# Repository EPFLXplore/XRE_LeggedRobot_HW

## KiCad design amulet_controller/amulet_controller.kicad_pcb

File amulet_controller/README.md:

<p align="center" width="100%">
  <source media="(prefers-color-scheme: dark)" width="33%" srcset="./Logos/amulet_logo_light.svg">
  <source media="(prefers-color-scheme: light)" width="33%" srcset="./Logos/amulet_logo.svg">
  
</p>

<h1 align="center">Λ M U L E T</h1>

ΛMULET is a high-power brushless motor controller, compatible with the [moteus firmware](https://github.com/mjbots/moteus). It was specifically designed to be integrated in [EPFL Xplore](https://github.com/EPFLXplore)'s Legged Robot actuators.

***

## SPECIFICATIONS

| Parameter | ΛMULET V1.0 | 
| --- | --- |
| Voltage Input | 12-44V |
| Peak Electrical Power | TBD |
| Mass | TBD |
| Peak Phase Current | 100A |
| Communication | 5Mbps CAN-FD |
| Cooling | 12V Fan |
| Positioning | 2x Onboard 14-bit Encoders |
| Control rate | 15-30kHz |
| PWM Switching Rate | 15-60kHz |
| MCU | STM32G474 |
| Dimensions | 69.7 x 76.7mm |

***

## DIRECTORY STRUCTURE

```
amulet_controller
├── Computations     # Misc calculations
├── DXF_SVG          # Vector graphics
├── Images           # Pictures and screenshots
├── Logos            # Xplore and Amulet logos
├── Manufacturing
│   |── Assembly     # Position files, BOM, assembly document
|   |   └── ibom     # HTML BOM
|   └── Fabrication  # Fabrication document and testpoints positions
|       └── Gerbers  # Gerbers
├── STEP_Blender     # 3D STEP and pcb2blender file
├── Schematic        # PDF of schematic
├── Templates        # Title block templates
└── lib
    |── 3d_models    # Component 3D models
    |── lib_fp       # Footprint libraries
    └── lib_sym      # Symbol libraries
```

***

## FIRMWARE

[Associated firmware](https://github.com/EPFLXplore/XRE_moteus/tree/amulet) is forked from the [moteus](https://github.com/mjbots/moteus) repository.

***

## CREDITS

Schematic is hugely inspired by the moteus controllers designed by Josh Pieper. They were modified to meet our own specifications, and to follow what I personally consider good layout practices.

***

## PHOTOS

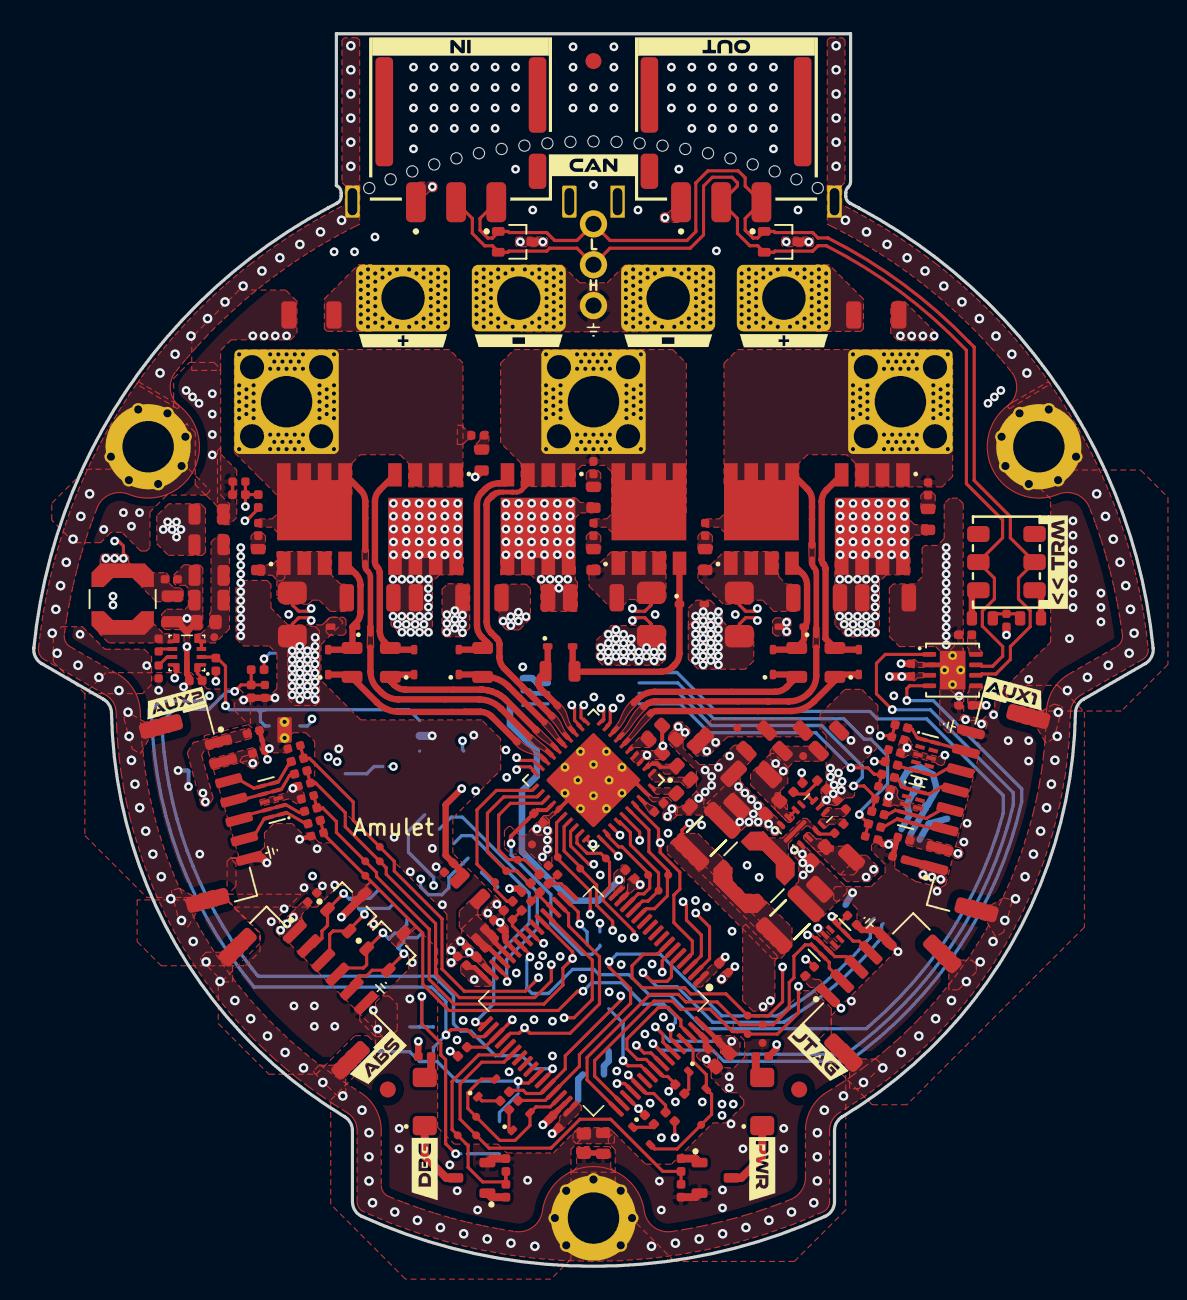
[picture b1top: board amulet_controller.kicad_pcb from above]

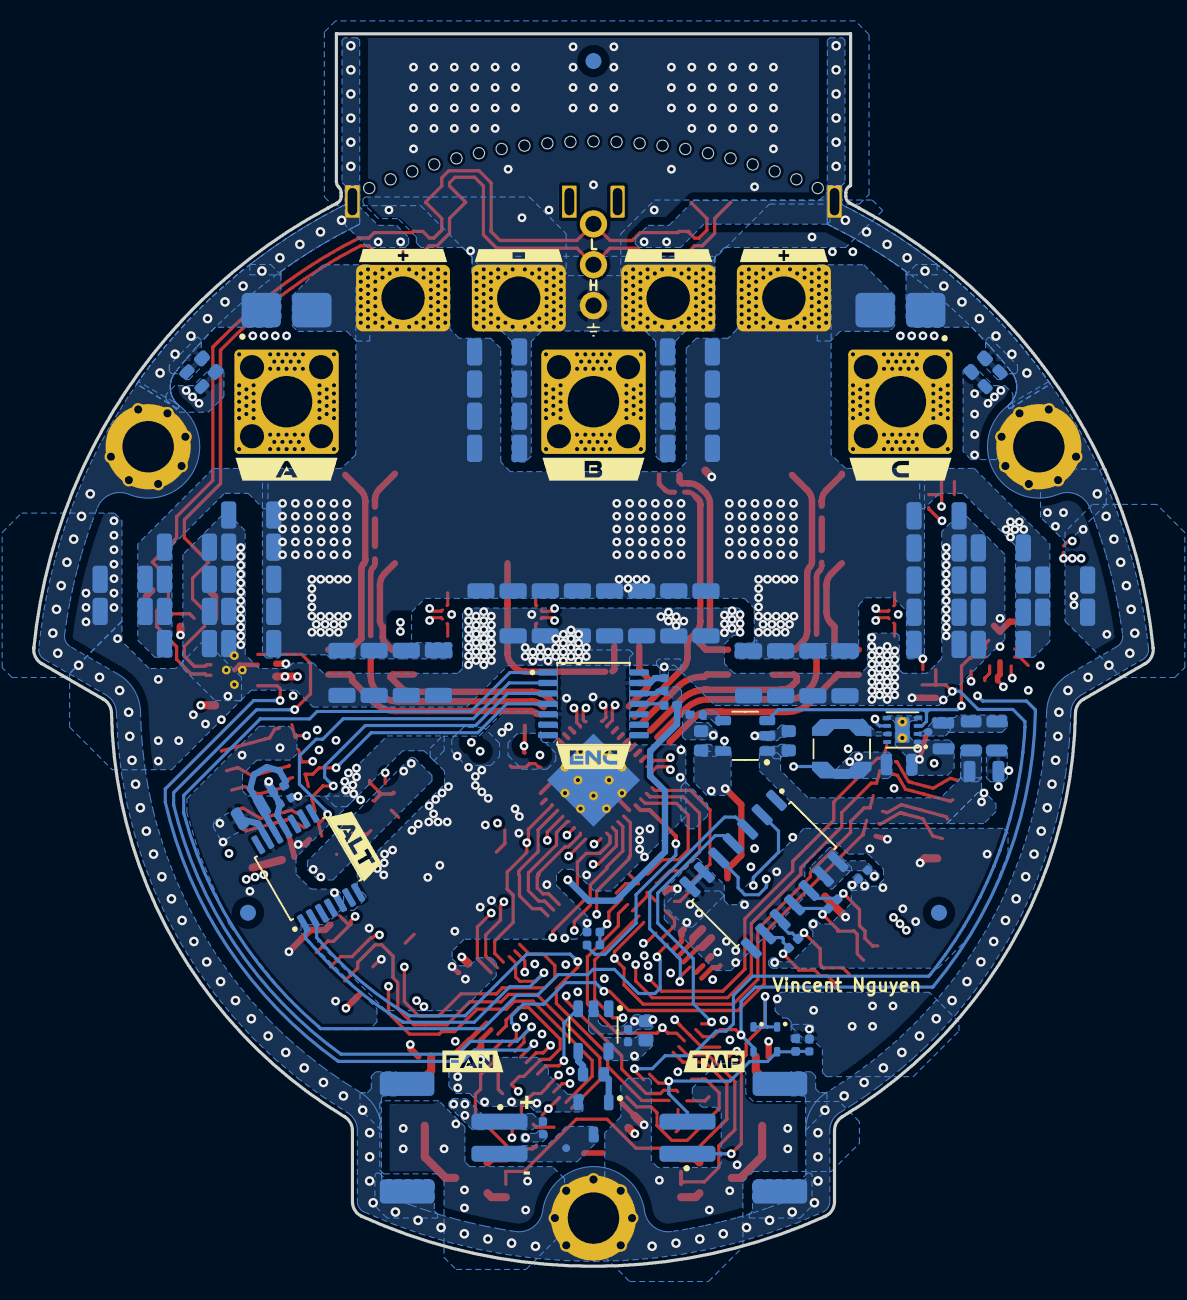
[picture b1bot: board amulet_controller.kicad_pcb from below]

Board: 6 copper layers, 69.7 x 76.7 mm, 413 parts (120 on the bottom side), 141 nets.

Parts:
C1, C84, C110: 4u7 X7R 16V; C_0603_1608_DensityHigh
C2, C6, C9, C24, C26: 1u X7R 10V; C_0402_1005_DensityHigh
C3, C4, C5, C8, C10, C11, C27, C28, C29, C101, C102, C103, C104, C105, C107, C108, C109, C111, C112, C113, C114, C115, C125, C126, C127, C128: 100n X7R 50V; C_0402_1005_DensityHigh
C7: 4u7 X5R 25V; C_0402_1005_DensityHigh
C12, C13, C14: 1n X7R 25V; C_0402_1005_DensityHigh
C15, C16, C17, C18, C20, C45, C52: 2u2 X7R 100V; R_0805_2012_DensityHigh
C19, C21, C31, C32, C33, C34, C35, C36, C39, C40, C41, C42, C43, C44, C46, C47, C48, C49, C50, C51, C53, C54, C55, C57, C58, C59, C61, C62, C63, C64, C65, C66, C67, C68, C69, C70, C71, C72, C73, C74, C75, C77, C78, C79, C80, C81, C82, C85, C86, C87: 4u7 X7R 100V; C_1206_3216_DensityHigh
C22, C92: 100n X7R 100V; C_0603_1608_DensityHigh
C23, C25: 220n X7S 100V; C_0603_1608_DensityHigh
C30, C38: 15u X7R 25V; C_1210_3225_DensityHigh
C37, C83: 22u X7R 10V; C_0805_2012_DensityHighest
C56, C106: 10u X7R 25V; C_0805_2012_DensityHighest
C60, C88, C93: 1u X7R 25V; C_0603_1608_DensityHigh
C76: 10n X7R 100V; C_0402_1005_DensityHigh
C89, C96, C98, C100: 4u7 X7R 100V; C_1206_3216_DensityHighest
C90: 100n X7R 16V; C_0402_1005_DensityHigh
C91: 47n X7R 100V; C_0603_1608_DensityHigh
C94: 1u X7R 6.3V; C_0402_1005_DensityHigh
C95, C97, C99: 100n X7R 100V; C_1206_3216_DensityHighest
C116, C117, C118, C119, C120, C121, C122, C123, C124, C133, C134, C135, C136, C137, C138: 3n3 X7R 100V; C_0402_1005_DensityHigh
C129: 4n7 X7R 100V; C_0402_1005_DensityHigh
C130, C131, C132: 1n X7R 1kV; C_0603_1608_DensityHigh
D1, D2: SMBJ51CD-M3/H; DIOM4336X24N
D3, D4, D5, D6, D7, D8, D9, D10, D11, D14, D15, D19, D20, D21, D22: BAT41KFILM; D_SOD-523
D12: YELLOW; LED_SM1206
D13: GREEN; LED_SM1206
D16, D17: PESD4USB5B-TBSX; SOT1176D
D18, D26: PESD4USB3U-TBSX; SOT1176D
D23, D27: CDSOT23-SM712; SOT95P230X110-3N
D24, D25: PESD2CANFD24V-UX; SOT95P230X117-3N
FB1, FB2, FB3, FB4: 1k @ 100MHz; R_0805_2012_DensityHigh
FM1, FM2, FM3, FM4, FM5, FM6: Fiducial; Fiducial_1mm_Mask2mm
H1, H2, H3: M3; MountingHole_3.2mm_M3_Pad_Via
J1: XT60PW-F; AMASS_XT60PW-F_1x02_P7.20mm_Horizontal
J2: XT60PW-M; AMASS_XT60PW-M_1x02_P7.20mm_Horizontal
J3: Phase A; Pad_Square_Vias_6.5x6.5mm
J4: Phase B; Pad_Square_Vias_6.5x6.5mm
J5: Phase C; Pad_Square_Vias_6.5x6.5mm
J6: SM08B-GHS-TB; JST_GH_SM08B-GHS-TB_1x08-1MP_P1.25mm_Horizontal
J7: SM07B-GHS-TB; JST_GH_SM07B-GHS-TB_1x07-1MP_P1.25mm_Horizontal
J8, J9: S2B-PH-SM4-TB; JST_PH_S2B-PH-SM4-TB_1x02-1MP_P2.00mm_Horizontal
J10: SM06B-GHS-TB; JST_GH_SM06B-GHS-TB_1x06-1MP_P1.25mm_Horizontal
J11: PTH 01x03 2.54mm; PTH_1x03_P2.54mm
J12, J13: Nano-Fit 1x03; 1054301203
J14: SM05B-GHS-TB; JST_GH_SM05B-GHS-TB_1x05-1MP_P1.25mm_Horizontal
L1, L2: 22u; L_Coilcraft_LPS4018
L3: 2u2; L_Coilcraft_LPS3314
MB1, MB2, MB3, MB4, MB5, MB6, MB7, MB8, MB9, MB10, MB11, MB12, MB13, MB14, MB15, MB16, MB17, MB18, MB19, MB20, MB21: mousebites_single_0.7mm
NT1: FB_5V; NetTie-2_SMD_Pad0.2mm
NT2: FB_12V; NetTie-2_SMD_Pad0.2mm
NT3: VOS_3V3; NetTie-2_SMD_Pad0.2mm
NT4: SRC_HS_A; NetTie-2_SMD_Pad0.4mm
NT5: SHNTA_P; NetTie-2_SMD_Pad0.2mm
NT6: SHNTA_N; NetTie-2_SMD_Pad0.2mm
NT7: SRC_HS_B; NetTie-2_SMD_Pad0.3mm
NT8: SHNTB_P; NetTie-2_SMD_Pad0.2mm
NT9: SHNTB_N; NetTie-2_SMD_Pad0.2mm
NT10: SRC_HS_C; NetTie-2_SMD_Pad0.4mm
NT11: SHNTC_P; NetTie-2_SMD_Pad0.2mm
NT12: SHNTC_N; NetTie-2_SMD_Pad0.2mm
NT13: NTC_MOT_H; NetTie-2_SMD_Pad0.2mm
NT14: NTC_MOT_L; NetTie-2_SMD_Pad0.2mm
Q1, Q2, Q3, Q4, Q5, Q6: TPW1R306PL,L1Q; 2-5S1A
Q7, Q8, Q9: PMV90ENER; SOT-23-3
R1, R2, R3: 22R 1%; R_0402_1005_DensityHigh
R4, R31, R32: 0R; R_0402_1005_DensityHigh
R5, R19, R20, R21, R24, R29: 100k 1%; R_0402_1005_DensityHigh
R6: 9k09 1%; R_0402_1005_DensityHigh
R7, R27, R33: 10k 1%; R_0402_1005_DensityHigh
R8, R9, R28, R44, R45, R46, R47: 2k 1%; R_0402_1005_DensityHigh
R10, R11, R13, R14, R16, R17: 7R5 1% 1/2W; R_0805_2012_DensityHigh
R12, R15, R18: 0m5 1% 2W; HCS1206FTL500
R22, R23, R25, R35, R36, R37, R38, R39, R40, R41, R42, R43, R48, R49: 100R 1% 1/5W; R_0402_1005_DensityHigh
R26: 150R 1% 1/5W; R_0402_1005_DensityHigh
R30: 4k7 1%; R_0402_1005_DensityHigh
R34: 10R 1%; R_0603_1608_DensityHigh
R50, R51: 60R4 1% 1/4W; R_0603_1608_DensityHigh
R52, R53, R54: 0R; R_0603_1608_DensityHigh
R55, R56, R57, R58, R59, R60: 5R 1% 0.4W; R_0603_1608_DensityHigh
SW1: CAS-220TA; CAS-220A_NDC-L
TH1: 47k 1% NTC; R_0402_1005_DensityHigh
TP1: MOTOR_ENABLE; TestPoint_Pad_D0.5mm
TP2: MOTOR_HIZ; TestPoint_Pad_D0.5mm
TP3: MOTOR_FAULT; TestPoint_Pad_D0.5mm
TP4: DRV_SCLK; TestPoint_Pad_D0.5mm
TP5: DRV_MISO; TestPoint_Pad_D0.5mm
TP6: DRV_MOSI; TestPoint_Pad_D0.5mm
TP7: DRV_CS; TestPoint_Pad_D0.5mm
TP8: PWM_PHASEA; TestPoint_Pad_D0.5mm
TP9: PWM_PHASEB; TestPoint_Pad_D0.5mm
TP10: PWM_PHASEC; TestPoint_Pad_D0.5mm
TP11: SOA; TestPoint_Pad_D0.5mm
TP12: SOB; TestPoint_Pad_D0.5mm
TP13: SOC; TestPoint_Pad_D0.5mm
TP14: SWDIO; TestPoint_Pad_D0.5mm
TP15: SWCLK; TestPoint_Pad_D0.5mm
TP16: NRST; TestPoint_Pad_D0.5mm
TP17: AUX1_A; TestPoint_Pad_D0.5mm
TP18: AUX1_B; TestPoint_Pad_D0.5mm
TP19: AUX1_C; TestPoint_Pad_D0.5mm
TP20: AUX1_D; TestPoint_Pad_D0.5mm
TP21: AUX1_E; TestPoint_Pad_D0.5mm
TP22: AUX1_I2C_PULLUP; TestPoint_Pad_D0.5mm
TP23: POS_SENSOR_CS; TestPoint_Pad_D0.5mm
TP24: AUX2_A; TestPoint_Pad_D0.5mm
TP25: AUX2_B; TestPoint_Pad_D0.5mm
TP26: AUX2_C; TestPoint_Pad_D0.5mm
TP27: AUX2_D; TestPoint_Pad_D0.5mm
TP28: AUX2_I2C_PULLUP; TestPoint_Pad_D0.5mm
TP29: RS422_RE; TestPoint_Pad_D0.5mm
TP30: RS422_DE; TestPoint_Pad_D0.5mm
TP31: LED_DBG; TestPoint_Pad_D0.5mm
TP32: LED_PWR; TestPoint_Pad_D0.5mm
TP33: FD_CAN_RX; TestPoint_Pad_D0.5mm
TP34: FDCAN_TX; TestPoint_Pad_D0.5mm
TP35: FAN_CTRL; TestPoint_Pad_D0.5mm
TP36: SENSE_TEMP_MOT; TestPoint_Pad_D0.5mm
TP37: SENSE_TEMP_FET; TestPoint_Pad_D0.5mm
TP38: SENSE_VBAT; TestPoint_Pad_D0.5mm
TP39, TP40, TP41: +VBAT; TestPoint_Pad_D0.5mm
TP42: F_VIN_12V; TestPoint_Pad_D0.5mm
TP43: F_VIN_5V; TestPoint_Pad_D0.5mm
TP44: F_VIN_3V3; TestPoint_Pad_D0.5mm
TP45: +12V; TestPoint_Pad_D0.5mm
TP46, TP47: +5V; TestPoint_Pad_D0.5mm
TP48, TP49, TP50: +3V3; TestPoint_Pad_D0.5mm
TP51: +A3V3; TestPoint_Pad_D0.5mm
TP52, TP53, TP54, TP55, TP56, TP57, TP58: GND; TestPoint_Pad_D0.5mm
TP59: GHA; TestPoint_Pad_D0.4mm
TP60: GLA; TestPoint_Pad_D0.4mm
TP61: SHA; TestPoint_Pad_D0.4mm
TP62: GHB; TestPoint_Pad_D0.4mm
TP63: GLB; TestPoint_Pad_D0.4mm
TP64: SHB; TestPoint_Pad_D0.4mm
TP65: GHC; TestPoint_Pad_D0.4mm
TP66: GLC; TestPoint_Pad_D0.4mm
TP67: SHC; TestPoint_Pad_D0.4mm
TP68: SA_P; TestPoint_Pad_D0.5mm
TP69: SA_N; TestPoint_Pad_D0.5mm
TP70: SB_P; TestPoint_Pad_D0.5mm
TP71: SB_N; TestPoint_Pad_D0.5mm
TP72: SC_P; TestPoint_Pad_D0.5mm
TP73: SC_N; TestPoint_Pad_D0.5mm
TP74: FAN_SW; TestPoint_Pad_D0.5mm
U1: STM32G474RET3; LQFP-64_10x10mm_P0.5mm
U2: LMR36506MSC5RPERQ1; LMR36503
U3: LMR36006FSCQ; LMR36006
U4: TPS62172DSG; WSON-8-1EP_2x2mm_P0.5mm_EP0.9x1.6mm_ThermalVias
U5: LP2992IM5-3.3/NOPB; SOT95P280X145-5N
U6: DRV8353FS; WQFN-40-1EP_6x6mm_P0.5mm_EP4.15x4.15mm_ThermalVias
U7: AS5047P; SOP-14_4.4x5mm_P0.65mm_H1.2mm
U8: AS5048B; SOP-14_4.4x5mm_P0.65mm_H1.2mm
U9: SN65HVD35DR; SOIC-14 5.4mm
U10: TCAN1051HGVDRBRQ1; HVSON-8-1EP_3x3mm_P0.65mm_EP1.6x2.4mm_ThermalVias
U11: DGD0216WT-7; SOT-23-5
kibuzzard-657CE6B7: G***; kibuzzard-657CE6B7
kibuzzard-657CE6F4: G***; kibuzzard-657CE6F4
kibuzzard-657CE8E9: G***; kibuzzard-657CE8E9
kibuzzard-657CE8F0: G***; kibuzzard-657CE8F0
kibuzzard-657CE701: G***; kibuzzard-657CE701
kibuzzard-657CE738: G***; kibuzzard-657CE738
kibuzzard-657DB620: G***; kibuzzard-657DB620
kibuzzard-657EBC7A: G***; kibuzzard-657EBC7A
kibuzzard-657EBC30: G***; kibuzzard-657EBC30
kibuzzard-657EBCD6: G***; kibuzzard-657EBCD6
kibuzzard-657EBD3F: G***; kibuzzard-657EBD3F
kibuzzard-657EBDD6: G***; kibuzzard-657EBDD6
kibuzzard-657EBE81: G***; kibuzzard-657EBE81
kibuzzard-657EBEA6: G***; kibuzzard-657EBEA6
kibuzzard-657F78ED, kibuzzard-657F78ED#2, kibuzzard-657F78ED#3, kibuzzard-657F78ED#4: G***; kibuzzard-657F78ED
kibuzzard-657F7953, kibuzzard-657F7953#2, kibuzzard-657F7953#3, kibuzzard-657F7953#4: G***; kibuzzard-657F7953
kibuzzard-65803F12: G***; kibuzzard-65803F12
kibuzzard-658032A4: G***; kibuzzard-658032A4
kibuzzard-6580330B: G***; kibuzzard-6580330B
kibuzzard-65807142: G***; kibuzzard-65807142
kibuzzard-65807156: G***; kibuzzard-65807156

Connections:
+3V3: C1.1, C3.1, C4.1, C5.1, C8.1, C9.1, C83.1, C104.1, C105.1, C107.1, C108.1, C114.1, C115.1, C127.1, J6.2, J7.2, J14.1, L3.2, NT3.2, R8.1, R9.1, R31.1, R32.1, TP48.1, TP49.1, TP50.1, U1.1 (VBAT), U1.16 (VDD), U1.32 (VDD), U1.48 (VDD), U1.64 (VDD), U7.12 (VDD3V3), U8.11 (VDD5V), U9.13 (VCC), U9.14 (VCC), U10.5 (VIO)
+5V: C29.1, C37.1, C45.1, C60.1, C109.1, C110.1, C111.1, C112.1, C113.1, C126.1, FB4.1, J6.1, J7.1, J10.1, L1.2, NT1.1, R7.2, R23.2, R26.1, TP46.1, TP47.1, U5.1 (VIN), U10.3 (VCC), U11.5 (VCC)
+12V: C30.1, C38.1, C125.1, J9.1, L2.2, NT2.2, TP45.1
+A3V3: C2.1, C84.1, C90.1, D14.1 (K), D15.1 (K), FB1.1, NT13.1, R19.1, TH1.1, TP51.1, U5.5 (VOUT), U6.24 (VREF)
+VBAT: C15.1, C16.1, C31.1, C32.1, C33.1, C34.1, C35.1, C36.1, C39.1, C40.1, C41.1, C42.1, C43.1, C44.1, C46.1, C47.1, C48.1, C49.1, C50.1, C51.1, C53.1, C54.1, C55.1, C57.1, C58.1, C59.1, C61.1, C62.1, C63.1, C64.1, C65.1, C66.1, C67.1, C68.1, C69.1, C70.1, C71.1, C72.1, C73.1, C74.1, C75.1, C77.1, C78.1, C79.1, C80.1, C81.1, C82.1, C85.1, C86.1, C87.1, C88.1, C89.1, C92.1, C95.1, C96.1, C97.1, C98.1, C99.1, C100.1, D1.2 (A2), D2.2 (A2), FB2.1, FB3.1, J1.2, J2.2, Q1.5 (D), Q1.6 (D), Q1.7 (D), Q1.8 (D), Q3.5 (D), Q3.6 (D), Q3.7 (D), Q3.8 (D), Q5.5 (D), Q5.6 (D), Q5.7 (D), Q5.8 (D), R29.1, R58.2, R59.2, R60.2, TP39.1, TP40.1, TP41.1, U6.3 (VM), U6.4 (VDRAIN)
/Project Architecture/Interface - FD-CAN/FDCAN_N: D24.1 (K1), D25.1 (K1), J11.3, J12.3, J13.3, SW1.2 (B), U10.6 (CANL)
/Project Architecture/Interface - FD-CAN/FDCAN_P: D24.2 (K2), D25.2 (K2), J11.2, J12.2, J13.2, SW1.5 (B), U10.7 (CANH)
/Project Architecture/Interface - FD-CAN/FDCAN_RX: TP33.1, U1.58 (PB5), U10.4 (RXD)
/Project Architecture/Interface - FD-CAN/FDCAN_S: R33.1, U10.8 (S)
/Project Architecture/Interface - FD-CAN/FDCAN_TX: TP34.1, U1.59 (PB6), U10.1 (TXD)
/Project Architecture/Interface - Fan Control/FAN_GATE: Q9.1 (G), R34.2
/Project Architecture/Interface - Fan Control/FAN_OUT: R34.1, U11.4 (OUT)
/Project Architecture/Interface - Fan Control/FAN_SW: J9.2, Q9.3 (D), TP74.1
/Project Architecture/Interface - Interconnects/AUX1P_A: D18.5 (K), D18.6 (K), J6.3, R35.1
/Project Architecture/Interface - Interconnects/AUX1P_B: D18.4 (K), D18.7 (K), J6.4, R36.1
/Project Architecture/Interface - Interconnects/AUX1P_C: D18.1 (K), D18.10 (K), J6.5, R37.1
/Project Architecture/Interface - Interconnects/AUX1P_D: D16.5 (K), D16.6 (K), J6.6, R38.1
/Project Architecture/Interface - Interconnects/AUX1P_E: D16.1 (K), D16.10 (K), J6.7, R39.1
/Project Architecture/Interface - Interconnects/AUX1_A: C124.1, R35.2, TP17.1, U1.19 (PA5), U1.36 (PB14), U7.2 (CLK)
/Project Architecture/Interface - Interconnects/AUX1_B: C122.1, R36.2, TP18.1, U1.57 (PB4), U7.3 (MISO)
/Project Architecture/Interface - Interconnects/AUX1_C: C120.1, R37.2, TP19.1, U1.21 (PA7), U7.4 (MOSI)
/Project Architecture/Interface - Interconnects/AUX1_D: C118.1, R38.2, R44.2, TP20.1, U1.51 (PA15), U9.2 (R)
/Project Architecture/Interface - Interconnects/AUX1_D_K: D19.1 (K), R44.1
/Project Architecture/Interface - Interconnects/AUX1_E: C116.1, R39.2, R46.2, TP21.1, U1.56 (PB3), U1.62 (PB9), U9.5 (D)
/Project Architecture/Interface - Interconnects/AUX1_E_K: D21.1 (K), R46.1
/Project Architecture/Interface - Interconnects/AUX1_I2C_PULLUP: D19.2 (A), D21.2 (A), TP22.1, U1.61 (PB8)
/Project Architecture/Interface - Interconnects/AUX2P_A: D17.5 (K), D17.6 (K), J7.3, R40.1
/Project Architecture/Interface - Interconnects/AUX2P_B: D17.4 (K), D17.7 (K), J7.4, R41.1
/Project Architecture/Interface - Interconnects/AUX2P_C: D17.2 (K), D17.9 (K), J7.5, R42.1
/Project Architecture/Interface - Interconnects/AUX2P_D: D17.1 (K), D17.10 (K), J7.6, R43.1
/Project Architecture/Interface - Interconnects/AUX2_A: C123.1, R40.2, TP24.1, U1.6 (PF1)
/Project Architecture/Interface - Interconnects/AUX2_B: C121.1, R41.2, R45.2, TP25.1, U1.5 (PF0), U1.44 (PA10), U8.1 (SDA)
/Project Architecture/Interface - Interconnects/AUX2_B_K: D20.1 (K), R45.1
/Project Architecture/Interface - Interconnects/AUX2_C: C119.1, R42.2, R47.2, TP26.1, U1.22 (PC4), U1.45 (PA11), U8.2 (SCL)
/Project Architecture/Interface - Interconnects/AUX2_C_K: D22.1 (K), R47.1
/Project Architecture/Interface - Interconnects/AUX2_D: C117.1, R43.2, TP27.1, U1.60 (PB7)
/Project Architecture/Interface - Interconnects/AUX2_I2C_PULLUP: D20.2 (A), D22.2 (A), TP28.1, U1.46 (PA12)
/Project Architecture/Interface - Interconnects/CAN_TERM_B: R51.2, SW1.4 (A)
/Project Architecture/Interface - Interconnects/CAN_TERM_MID: C129.1, R50.2, R51.1
/Project Architecture/Interface - Interconnects/CAN_TERM_T: R50.1, SW1.1 (A)
/Project Architecture/Interface - Interconnects/NRST: C128.1, D26.1 (K), D26.10 (K), J14.4, TP16.1, U1.7 (PG10)
/Project Architecture/Interface - Interconnects/NTC_MOT_H: J8.1, NT13.2
/Project Architecture/Interface - Interconnects/NTC_MOT_L: J8.2, NT14.2
/Project Architecture/Interface - Interconnects/POS_SENSOR_CS: TP23.1, U1.26 (PB2), U7.1 (~CS)
/Project Architecture/Interface - Interconnects/RS422_D+: D23.2 (A2), J10.5, R49.2, U9.9 (Y)
/Project Architecture/Interface - Interconnects/RS422_D-: D23.1 (A1), J10.4, R49.1, U9.10 (Z)
/Project Architecture/Interface - Interconnects/RS422_R+: D27.1 (A1), J10.2, R48.1, U9.12 (A)
/Project Architecture/Interface - Interconnects/RS422_R-: D27.2 (A2), J10.3, R48.2, U9.11 (B)
/Project Architecture/Interface - Interconnects/SWCLK: D26.4 (K), D26.7 (K), J14.3, TP15.1, U1.50 (PA14)
/Project Architecture/Interface - Interconnects/SWDIO: D26.5 (K), D26.6 (K), J14.2, TP14.1, U1.49 (PA13)
/Project Architecture/Interface - RS-422/RS422_DE: TP30.1, U1.33 (PB11), U9.4 (DE)
/Project Architecture/Interface - RS-422/RS422_~RE: TP29.1, U1.30 (PB10), U9.3 (~RE)
/Project Architecture/MCU - IOs/BOARD_VERSION: R19.2, R20.1, U1.18 (PA4)
/Project Architecture/MCU - IOs/DRV_CS: TP7.1, U1.24 (PB0), U6.30 (nSCS)
/Project Architecture/MCU - IOs/DRV_MISO: R9.2, TP5.1, U1.53 (PC11), U6.27 (SDO)
/Project Architecture/MCU - IOs/DRV_MOSI: TP6.1, U1.2 (PC13), U6.28 (SDI)
/Project Architecture/MCU - IOs/DRV_SCLK: TP4.1, U1.52 (PC10), U6.29 (SCLK)
/Project Architecture/MCU - IOs/FAN_CTRL: TP35.1, U1.55 (PD2), U11.3 (IN)
/Project Architecture/MCU - IOs/FILTER_SOA: C12.1, R1.1, U1.17 (PA3)
/Project Architecture/MCU - IOs/FILTER_SOB: C13.1, R2.1, U1.20 (PA6)
/Project Architecture/MCU - IOs/FILTER_SOC: C14.1, R3.1, U1.25 (PB1)
/Project Architecture/MCU - IOs/LED_DBG: R21.1, R22.1, TP31.1, U1.37 (PB15)
/Project Architecture/MCU - IOs/LED_PWR: R24.1, R25.1, TP32.1, U1.38 (PC6)
/Project Architecture/MCU - IOs/MOTOR_ENABLE: TP1.1, U1.3 (PC14), U6.31 (ENABLE)
/Project Architecture/MCU - IOs/MOTOR_FAULT: R8.2, TP3.1, U1.35 (PB13), U6.26 (nFAULT)
/Project Architecture/MCU - IOs/MOTOR_HIZ: TP2.1, U1.4 (PC15), U6.33 (INLA), U6.35 (INLB), U6.37 (INLC)
/Project Architecture/MCU - IOs/PWM_PHASEA: TP8.1, U1.14 (PA2), U6.32 (INHA)
/Project Architecture/MCU - IOs/PWM_PHASEB: TP9.1, U1.13 (PA1), U6.34 (INHB)
/Project Architecture/MCU - IOs/PWM_PHASEC: TP10.1, U1.12 (PA0), U6.36 (INHC)
/Project Architecture/MCU - IOs/SENSE_TEMP_FET: C101.1, D14.2 (A), R27.1, TH1.2, TP37.1, U1.34 (PB12)
/Project Architecture/MCU - IOs/SENSE_TEMP_MOT: C102.1, D15.2 (A), NT14.1, R28.1, TP36.1, U1.42 (PA8)
/Project Architecture/MCU - IOs/SENSE_VBAT: C103.1, R29.2, R30.1, TP38.1, U1.43 (PA9)
/Project Architecture/MCU - IOs/SOA: R1.2, TP11.1, U6.23 (SOA)
/Project Architecture/MCU - IOs/SOB: R2.2, TP12.1, U6.22 (SOB)
/Project Architecture/MCU - IOs/SOC: R3.2, TP13.1, U6.21 (SOC)
/Project Architecture/MCU - Power/F_A3V3: C6.1, C7.1, C10.1, C11.1, FB1.2, U1.28 (VREF+), U1.29 (VDDA)
/Project Architecture/Motor Control - Top Level/CPH: C91.1, U6.2 (CPH)
/Project Architecture/Motor Control - Top Level/CPL: C91.2, U6.1 (CPL)
/Project Architecture/Motor Control - Top Level/DVDD: C94.1, U6.38 (DVDD)
/Project Architecture/Motor Control - Top Level/GHA: D4.1 (K), R10.2, TP59.1, U6.6 (GHA)
/Project Architecture/Motor Control - Top Level/GHB: D7.1 (K), R13.1, TP62.1, U6.15 (GHB)
/Project Architecture/Motor Control - Top Level/GHC: D10.1 (K), R16.1, TP65.1, U6.16 (GHC)
/Project Architecture/Motor Control - Top Level/GLA: D5.1 (K), R11.1, TP60.1, U6.8 (GLA)
/Project Architecture/Motor Control - Top Level/GLB: D8.1 (K), R14.1, TP63.1, U6.13 (GLB)
/Project Architecture/Motor Control - Top Level/GLC: D11.1 (K), R17.1, TP66.1, U6.18 (GLC)
/Project Architecture/Motor Control - Top Level/Motor Control - Inverter/FET_GHA: D4.2 (A), Q1.4 (G), R10.1
/Project Architecture/Motor Control - Top Level/Motor Control - Inverter/FET_GHB: D7.2 (A), Q3.4 (G), R13.2
/Project Architecture/Motor Control - Top Level/Motor Control - Inverter/FET_GHC: D10.2 (A), Q5.4 (G), R16.2
/Project Architecture/Motor Control - Top Level/Motor Control - Inverter/FET_GLA: D3.1 (K), D5.2 (A), Q2.4 (G), R11.2
/Project Architecture/Motor Control - Top Level/Motor Control - Inverter/FET_GLB: D6.1 (K), D8.2 (A), Q4.4 (G), R14.2
/Project Architecture/Motor Control - Top Level/Motor Control - Inverter/FET_GLC: D9.1 (K), D11.2 (A), Q6.4 (G), R17.2
/Project Architecture/Motor Control - Top Level/Motor Control - Inverter/PHA: C133.2, C136.1, J3.1, NT4.2, Q1.1 (S), Q1.2 (S), Q1.3 (S), Q2.5 (D), Q2.6 (D), Q2.7 (D), Q2.8 (D)
/Project Architecture/Motor Control - Top Level/Motor Control - Inverter/PHB: C134.2, C137.1, J4.1, NT7.2, Q3.1 (S), Q3.2 (S), Q3.3 (S), Q4.5 (D), Q4.6 (D), Q4.7 (D), Q4.8 (D)
/Project Architecture/Motor Control - Top Level/Motor Control - Inverter/PHC: C135.2, C138.1, J5.1, NT10.2, Q5.1 (S), Q5.2 (S), Q5.3 (S), Q6.5 (D), Q6.6 (D), Q6.7 (D), Q6.8 (D)
/Project Architecture/Motor Control - Top Level/Motor Control - Inverter/SNUBH_A: C136.2, R58.1
/Project Architecture/Motor Control - Top Level/Motor Control - Inverter/SNUBH_B: C137.2, R59.1
/Project Architecture/Motor Control - Top Level/Motor Control - Inverter/SNUBH_C: C138.2, R60.1
/Project Architecture/Motor Control - Top Level/Motor Control - Inverter/SNUBL_A: C133.1, R55.2
/Project Architecture/Motor Control - Top Level/Motor Control - Inverter/SNUBL_B: C134.1, R56.2
/Project Architecture/Motor Control - Top Level/Motor Control - Inverter/SNUBL_C: C135.1, R57.2
/Project Architecture/Motor Control - Top Level/Motor Control - Inverter/SRC_LS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: C95.2, NT5.1, Q2.1 (S), Q2.2 (S), Q2.3 (S), R12.2, R55.1
/Project Architecture/Motor Control - Top Level/Motor Control - Inverter/SRC_LS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: C97.2, NT8.2, Q4.1 (S), Q4.2 (S), Q4.3 (S), R15.2, R56.1
/Project Architecture/Motor Control - Top Level/Motor Control - Inverter/SRC_LS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: C99.2, NT11.2, Q6.1 (S), Q6.2 (S), Q6.3 (S), R18.2, R57.1
/Project Architecture/Motor Control - Top Level/SA_N: NT6.1, TP69.1, U6.10 (SNA)
/Project Architecture/Motor Control - Top Level/SA_P: NT5.2, TP68.1, U6.9 (SPA)
/Project Architecture/Motor Control - Top Level/SB_N: NT9.1, TP71.1, U6.11 (SNB)
/Project Architecture/Motor Control - Top Level/SB_P: NT8.1, TP70.1, U6.12 (SPB)
/Project Architecture/Motor Control - Top Level/SC_N: NT12.1, TP73.1, U6.20 (SNC)
/Project Architecture/Motor Control - Top Level/SC_P: NT11.1, TP72.1, U6.19 (SPC)
/Project Architecture/Motor Control - Top Level/SHA: NT4.1, TP61.1, U6.7 (SHA)
/Project Architecture/Motor Control - Top Level/SHB: NT7.1, TP64.1, U6.14 (SHB)
/Project Architecture/Motor Control - Top Level/SHC: NT10.1, TP67.1, U6.17 (SHC)
/Project Architecture/Motor Control - Top Level/VCP: C88.2, U6.5 (VCP)
/Project Architecture/Motor Control - Top Level/VGLS: C93.1, U6.40 (VGLS)
/Project Architecture/Power - Generation/ADJ_A3V3: C76.1, U5.4 (ADJ)
/Project Architecture/Power - Generation/BOOT_5V: C27.2, U2.6 (BOOT)
/Project Architecture/Power - Generation/BOOT_12V: C28.2, U3.4 (BOOT)
/Project Architecture/Power - Generation/FB_5V: NT1.2, U2.8 (FB)
/Project Architecture/Power - Generation/FB_12V: NT2.1, R5.1
/Project Architecture/Power - Generation/FB_DIV_12V: R5.2, R6.1, U3.7 (FB)
/Project Architecture/Power - Generation/F_VIN_3V3: C52.1, C56.1, FB4.2, TP44.1, U4.2 (VIN)
/Project Architecture/Power - Generation/F_VIN_5V: C17.1, C20.1, C22.1, FB2.2, TP43.1, U2.3 (EN/UVLO), U2.4 (VIN)
/Project Architecture/Power - Generation/F_VIN_12V: C18.1, C19.1, C21.1, C23.1, C25.1, FB3.2, TP42.1, U3.2 (VIN), U3.9 (EN), U3.10 (VIN)
/Project Architecture/Power - Generation/MODE_5V: R4.1, U2.1 (MODE/SYNC)
/Project Architecture/Power - Generation/PG_5V: R7.1, U2.2 (PGOOD), U4.3 (EN), U5.3 (ON/~OFF)
/Project Architecture/Power - Generation/SW_3V3: L3.1, U4.7 (SW)
/Project Architecture/Power - Generation/SW_5V: C27.1, L1.1, U2.5 (SW)
/Project Architecture/Power - Generation/SW_12V: C28.1, L2.1, U3.3 (NC), U3.12 (SW)
/Project Architecture/Power - Generation/VCC_5V: C24.1, U2.7 (VCC)
/Project Architecture/Power - Generation/VCC_12V: C26.1, U3.5 (VCC)
/Project Architecture/Power - Generation/VOS_3V3: NT3.1, U4.6 (VOS)
/Project Architecture/Sensing - Position/COMM_VDD: R31.2, U7.11 (VDD)
/Project Architecture/Sensing - Position/DIS_VDD3V: C106.1, R32.2, U8.12 (VDD3V)
/Project Architecture/User - LED Indicators/DBG_G: Q7.1 (G), R22.2
/Project Architecture/User - LED Indicators/LED_DBG_A: D12.2 (A), R23.1
/Project Architecture/User - LED Indicators/LED_DBG_K: D12.1 (K), Q7.3 (D)
/Project Architecture/User - LED Indicators/LED_PWR_A: D13.2 (A), R26.2
/Project Architecture/User - LED Indicators/LED_PWR_K: D13.1 (K), Q8.3 (D)
/Project Architecture/User - LED Indicators/PWR_G: Q8.1 (G), R25.2
CHASSIS: C130.1, C131.1, C132.1, D1.1 (A1), D2.1 (A1), D24.3 (CC), D25.3 (CC), H1.1, H2.1, H3.1, J1.MP2, J2.MP2, J6.MP1, J6.MP2, J7.MP1, J7.MP2, J8.MP1, J8.MP2, J9.MP1, J9.MP2, J10.MP1, J10.MP2, J14.MP1, J14.MP2, R52.1, R53.1, R54.1
GND: C1.2, C2.2, C3.2, C4.2, C5.2, C6.2, C7.2, C8.2, C9.2, C10.2, C11.2, C12.2, C13.2, C14.2, C15.2, C16.2, C17.2, C18.2, C19.2, C20.2, C21.2, C22.2, C23.2, C24.2, C25.2, C26.2, C29.2, C30.2, C31.2, C32.2, C33.2, C34.2, C35.2, C36.2, C37.2, C38.2, C39.2, C40.2, C41.2, C42.2, C43.2, C44.2, C45.2, C46.2, C47.2, C48.2, C49.2, C50.2, C51.2, C52.2, C53.2, C54.2, C55.2, C56.2, C57.2, C58.2, C59.2, C60.2, C61.2, C62.2, C63.2, C64.2, C65.2, C66.2, C67.2, C68.2, C69.2, C70.2, C71.2, C72.2, C73.2, C74.2, C75.2, C76.2, C77.2, C78.2, C79.2, C80.2, C81.2, C82.2, C83.2, C84.2, C85.2, C86.2, C87.2, C89.2, C90.2, C92.2, C93.2, C94.2, C96.2, C98.2, C100.2, C101.2, C102.2, C103.2, C104.2, C105.2, C106.2, C107.2, C108.2, C109.2, C110.2, C111.2, C112.2, C113.2, C114.2, C115.2, C116.2, C117.2, C118.2, C119.2, C120.2, C121.2, C122.2, C123.2, C124.2, C125.2, C126.2, C127.2, C128.2, C129.2, C130.2, C131.2, C132.2, D3.2 (A), D6.2 (A), D9.2 (A), D16.3 (A), D16.8 (A), D17.3 (A), D17.8 (A), D18.3 (A), D18.8 (A), D23.3 (common), D26.3 (A), D26.8 (A), D27.3 (common), J1.1, J2.1, J6.8, J7.7, J10.6, J11.1, J12.1, J13.1, J14.5, NT6.2, NT9.2, NT12.2, Q7.2 (S), Q8.2 (S), Q9.2 (S), R4.2, R6.2, R12.1, R15.1, R18.1, R20.2, R21.2, R24.2, R27.2, R28.2, R30.2, R33.2, R52.2, R53.2, R54.2, TP52.1, TP53.1, TP54.1, TP55.1, TP56.1, TP57.1, TP58.1, U1.15 (VSS), U1.27 (VSSA), U1.31 (VSS), U1.47 (VSS), U1.63 (VSS), U2.9 (GND), U3.1 (PGND), U3.6 (AGND), U3.11 (PGND), U4.1 (PGND), U4.4 (AGND), U4.5 (FB), U4.9 (PAD), U5.2 (GND), U6.25 (AGND), U6.39 (GND), U6.41 (EP), U7.5 (TST), U7.13 (GND), U8.5 (TEST), U8.13 (GND), U9.6 (GND), U9.7 (GND), U10.2 (GND), U10.9 (PAD), U11.2 (COM)

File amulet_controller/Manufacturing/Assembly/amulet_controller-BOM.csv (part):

Item,Qty,Reference(s),Value,Datasheet,Footprint,Description,Manufacturer,Manufacturer Part Number,Supplier 1,Supplier Part Number 1
1,3,"C1, 84, 110",4u7 X7R 16V,https://search.murata.co.jp/Ceramy/image/img/A01X/G101/ENG/G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,0_capacitor_smd:C_0603_1608_DensityHigh,4.7 µF ±10% 16V Ceramic Capacitor X7R 0603 (1608 Metric),Murata Electronics,GRM188Z71C475KE21J,Digikey,490-GRM188Z71C475KE21JCT-ND
2,5,"C2, 6, 9, 24, 26",1u X7R 10V,https://search.murata.co.jp/Ceramy/image/img/A01X/G101/ENG/G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,0_capacitor_smd:C_0402_1005_DensityHigh,1 µF ±10% 10V Ceramic Capacitor X7R 0402 (1005 Metric),Murata Electronics,GRM155Z71A105KE01J,Digikey,490-GRM155Z71A105KE01JCT-ND
3,26,"C3-5, 8, 10-11, 27-29, 101-05, 107-09, 111-15, 125-28",100n X7R 50V,https://search.murata.co.jp/Ceramy/image/img/A01X/G101/ENG/G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,0_capacitor_smd:C_0402_1005_DensityHigh,0.1 µF ±10% 50V Ceramic Capacitor X7R 0402 (1005 Metric),Murata Electronics,GCM155R71H104KE02J,Digikey,490-14514-1-ND
4,1,C7,4u7 X5R 25V,https://datasheets.kyocera-avx.com/cx5r.pdf,0_capacitor_smd:C_0402_1005_DensityHigh,4.7 µF ±20% 25V Ceramic Capacitor X5R 0402 (1005 Metric),KYOCERA AVX,04023D475MAT2A,Digikey,478-04023D475MAT2ACT-ND
5,3,C12-14,1n X7R 25V,https://www.yageo.com/upload/media/product/app/datasheet/mlc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,0_capacitor_smd:C_0402_1005_DensityHigh,1000 pF ±10% 25V Ceramic Capacitor X7R 0402 (1005 Metric),YAGEO,AC0402KRX7R8BB102,Digikey,311-3065-1-ND
6,7,"C15-18, 20, 45, 52",2u2 X7R 100V,https://product.tdk.com/system/files/dam/doc/product/capacit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,0_resistor_smd:R_0805_2012_DensityHigh,Multilayer Ceramic Capacitors MLCC - SMD/SMT 0805 100VDC 2.2uF 10% 1.25mm AEC-Q200,TDK Corporation,CGA4J1X7R2A225K125AC,Mouser,810-CGA4J7R2A225K125
7,50,"C19, 21, 31-36, 39-44, 46-51, 53-55, 57-59, 61-75, 77-82, 85-87",4u7 X7R 100V,https://search.murata.co.jp/Ceramy/image/img/A01X/G101/ENG/G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,0_capacitor_smd:C_1206_3216_DensityHigh,4.7 µF ±10% 100V Ceramic Capacitor X7R 1206 (3216 Metric),Murata Electronics,GRJ31CZ72A475KE01L,Digikey,490-GRJ31CZ72A475KE01LCT-ND
8,2,"C22, 92",100n X7R 100V,https://mm.digikey.com/Volume0/opasdata/d220001/medias/docus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,0_capacitor_smd:C_0603_1608_DensityHigh,0.1 µF ±10% 100V Ceramic Capacitor X7R 0603 (1608 Metric),Taiyo Yuden,HMK107B7104KAHT,Digikey,587-6009-1-ND
9,2,"C23, 25",220n X7S 100V,https://mm.digikey.com/Volume0/opasdata/d220001/medias/docus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,0_capacitor_smd:C_0603_1608_DensityHigh,0.22 µF ±10% 100V Ceramic Capacitor X7S 0603 (1608 Metric),Taiyo Yuden,HMK107C7224KAHTE,Digikey,587-5012-1-ND
10,2,"C30, 38",15u X7R 25V,https://product.tdk.com/system/files/dam/doc/product/capacit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,0_capacitor_smd:C_1210_3225_DensityHigh,15 µF ±20% 25V Ceramic Capacitor X7R 1210 (3225 Metric),TDK Corporation,CGA6M3X7R1E156M200AB,Digikey,445-175431-1-ND
11,2,"C37, 83",22u X7R 10V,https://search.murata.co.jp/Ceramy/image/img/A01X/G101/ENG/G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,0_capacitor_smd:C_0805_2012_DensityHighest,22 µF ±20% 10V Ceramic Capacitor X7R 0805 (2012 Metric),Murata Electronics,GRM21BZ71A226ME15L,Digikey,490-GRM21BZ71A226ME15LCT-ND
12,2,"C56, 106",10u X7R 25V,https://search.murata.co.jp/Ceramy/image/img/A01X/G101/ENG/G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,0_capacitor_smd:C_0805_2012_DensityHighest,10 µF ±10% 25V Ceramic Capacitor X7R 0805 (2012 Metric),Murata Electronics,GRM21BZ71E106KE15L,Digikey,490-GRM21BZ71E106KE15LCT-ND
13,3,"C60, 88, 93",1u X7R 25V,https://mm.digikey.com/Volume0/opasdata/d220001/medias/docus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,0_capacitor_smd:C_0603_1608_DensityHigh,1 µF ±10% 25V Ceramic Capacitor X7R 0603 (1608 Metric),Taiyo Yuden,TMK107AB7105KAHT,Digikey,587-3467-1-ND
14,1,C76,10n X7R 100V,https://mm.digikey.com/Volume0/opasdata/d220001/medias/docus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,0_capacitor_smd:C_0402_1005_DensityHigh,10000 pF ±10% 100V Ceramic Capacitor X7R 0402 (1005 Metric),Taiyo Yuden,HMR105B7103KV-F,Digikey,587-HMR105B7103KV-FCT-ND
15,4,"C89, 96, 98, 100",4u7 X7R 100V,https://search.murata.co.jp/Ceramy/image/img/A01X/G101/ENG/G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,0_capacitor_smd:C_1206_3216_DensityHighest,4.7 µF ±10% 100V Ceramic Capacitor X7R 1206 (3216 Metric),Murata Electronics,GRJ31CZ72A475KE01L,Digikey,490-GRJ31CZ72A475KE01LCT-ND
16,1,C90,100n X7R 16V,https://search.murata.co.jp/Ceramy/image/img/A01X/G101/ENG/G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,0_capacitor_smd:C_0402_1005_DensityHigh,0.1 µF ±10% 16V Ceramic Capacitor X7R 0402 (1005 Metric),Murata Electronics,GCM155R71C104KA55D,Digikey,490-4759-1-ND
17,1,C91,47n X7R 100V,https://connect.kemet.com:7667/gateway/IntelliData-Component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,0_capacitor_smd:C_0603_1608_DensityHigh,0.047 µF ±10% 100V Ceramic Capacitor X7R 0603 (1608 Metric),KEMET,C0603C473K1RECAUTO,Digikey,399-14764-1-ND
18,1,C94,1u X7R 6.3V,https://search.murata.co.jp/Ceramy/image/img/A01X/G101/ENG/G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,0_capacitor_smd:C_0402_1005_DensityHigh,1 µF ±10% 6.3V Ceramic Capacitor X7R 0402 (1005 Metric),Murata Electronics,GRT155R70J105KE01D,Digikey,490-18216-1-ND
19,3,"C95, 97, 99",100n X7R 100V,https://connect.kemet.com:7667/gateway/IntelliData-Component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,0_capacitor_smd:C_1206_3216_DensityHighest,0.1 µF ±10% 100V Ceramic Capacitor X7R 1206 (3216 Metric),KEMET,C1206C104K1RACAUTO,Digikey,399-7008-1-ND
20,1,C129,4n7 X7R 100V,https://www.murata.com/-/media/webrenewal/support/library/ca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,0_capacitor_smd:C_0402_1005_DensityHigh,4700 pF ±10% 100V Ceramic Capacitor X7R 0402 (1005 Metric),Murata Electronics,GCM155R72A472KA37D,Digikey,490-4765-1-ND
21,3,C130-32,1n X7R 1kV,https://connect.kemet.com:7667/gateway/IntelliData-Component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,0_capacitor_smd:C_0603_1608_DensityHigh,1000 pF ±10% 1000V (1kV) Ceramic Capacitor X7R 0603 (1608 Metric),KEMET,C0603V102KDRAC7867,Digikey,399-12306-1-ND
22,6,C133-38,3n3 X7R 100V,https://search.murata.co.jp/Ceramy/image/img/A01X/G101/ENG/G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,0_capacitor_smd:C_0402_1005_DensityHigh,3300 pF ±10% 100V Ceramic Capacitor X7R 0402 (1005 Metric),Murata Electronics,GRM155R72A332KA01D,Digikey,490-8261-1-ND
23,2,D1-2,SMBJ51CD-M3/H,https://www.vishay.com/docs/87606/smbj5cdthrusmbj120cd.pdf,0_diode_smd:DIOM4336X24N,Surface-Mount TRANSZORB® Transient Voltage Suppressors,Vishay,SMBJ51CD-M3/H,Digikey,SMBJ51CD-M3/HGICT-ND
24,15,"D3-11, 14-15, 19-22",BAT41KFILM,https://www.st.com/content/ccc/resource/technical/document/d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,0_diode_smd:D_SOD-523,Diode 100 V 200mA Surface Mount SOD-523,STMicroelectronics,BAT41KFILM,Digikey,497-5556-1-ND
25,1,D12,YELLOW,https://www.bivar.com/parts_content/Datasheets/SM1206NYC-IL.pdf,0_led_smd:LED_SM1206,Yellow 592nm LED Indication - Discrete 2V 1206 (3216 Metric),Bivar Inc.,SM1206NYC-IL,Digikey,492-1947-1-ND
26,1,D13,GREEN,https://www.bivar.com/parts_content/Datasheets/SM1206NPGC-IL.pdf,0_led_smd:LED_SM1206,Green 525nm LED Indication - Discrete 3V 1206 (3216 Metric),Bivar Inc.,SM1206NPGC-IL,Digikey,492-1945-1-ND
27,2,D16-17,PESD4USB5B-TBSX,https://assets.nexperia.com/documents/data-sheet/PESD4USB5B-TBS.pdf,0_package_DFN_QFN:SOT1176D,"5.5V (Typ) Clamp 7A (8/20µs) Ipp Tvs Diode Surface Mount, Wettable Flank DFN2510D-10",Nexperia USA Inc.,PESD4USB5B-TBSX,Digikey,1727-PESD4USB5B-TBSXCT-ND
28,2,"D18, 26",PESD4USB3U-TBSX,https://assets.nexperia.com/documents/data-sheet/PESD4USB3U-TBS.pdf,0_package_DFN_QFN:SOT1176D,"3.5V (Typ) Clamp 7A (8/20µs) Ipp Tvs Diode Surface Mount, Wettable Flank DFN2510D-10",Nexperia USA Inc.,PESD4USB3U-TBSX,Digikey,1727-PESD4USB3U-TBSXCT-ND
29,2,"D23, 27",CDSOT23-SM712,https://www.bourns.com/docs/Product-Datasheets/CDSOT23-SM712.pdf,0_package_SOT_TO_SMD:SOT95P230X110-3N,"26V, 14V Clamp 17A (8/20µs) Ipp Tvs Diode Surface Mount SOT-23-3",Bourns Inc.,CDSOT23-SM712,Digikey,CDSOT23-SM712CT-ND
30,2,D24-25,PESD2CANFD24V-UX,https://assets.nexperia.com/documents/data-sheet/PESD2CANFD2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,0_package_SOT_TO_SMD:SOT95P230X117-3N,42V Clamp 2.6A (8/20µs) Ipp Tvs Diode Surface Mount SOT-323,Nexperia USA Inc.,PESD2CANFD24V-UX,Digikey,1727-PESD2CANFD24V-UXCT-ND
31,4,FB1-4,1k @ 100MHz,https://www.we-online.com/katalog/datasheet/742792096.pdf,0_resistor_smd:R_0805_2012_DensityHigh,1 kOhms @ 100 MHz 1 Signal Line Ferrite Bead 0805 (2012 Metric) 1A 300mOhm,Würth Elektronik,742792096,Digikey,732-4648-1-ND
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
